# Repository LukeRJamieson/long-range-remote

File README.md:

# Long-range universal remote (Lite, 4 × AA)

A hand-held universal IR remote with far more range than a normal one. A head of 66 narrow-beam
(±5°) SFH 4545 emitters sits at the front of a 107 × 52 × 170 mm block. Behind it are:

- the Waveshare **ESP32-S3-RLCD-4.2** display, at the front of the top deck;
- a D-pad, a SELECT key and a BACK key behind the display, under your thumbs, so your hands never
  cover the screen;
- a bay for **four AA NiMH cells** underneath, which power the LEDs only. You take them out and
  charge them in any NiMH charger. The display board and ESP32 run from the display board's own
  18650, charged through its USB-C.

Everything is menu driven from the screen, or from a phone over Wi-Fi.

There are two boards, both within JLCPCB's cheapest 100 × 100 mm tier:

| Board | Size | What's on it |
|---|---|---|
| LED head | 99.8 × 44.8 mm, R3 corners | 66 × SFH 4545 (14 × 5 grid, corners left for the M3 holes) in 33 strings of 2, one 24 Ω 1206 resistor per string |
| Control | 82 × 52 mm | D-pad + SELECT + BACK (six 6 mm keys, straight to ESP32 GPIOs), the ESP32-switched power gate for the AA pack, the LED switch (a logic-level MOSFET driven straight from a GPIO), the pack-voltage divider, display and LED-head connectors |

KiCad 7 format; it opens in KiCad 7, 8 or 9.

## The system

```
 FRONT                                   top deck (lid)                                     BACK
 ┌──────────────┐  10-way ribbon  ┌────────────────────────┐ 16-way ribbon ┌──────────────────────┐
 │  LED HEAD    │◄════════════════│ CONTROL BOARD  82 x 52 │══════════════►│ Waveshare            │
 │ 99.8 x 44.8  │ J1 ↔ J5         │ D-pad, SELECT, BACK    │ J2 ↔ header   │ ESP32-S3-RLCD-4.2    │
 │ 66×SFH 4545  │ odd = LED_PWR   │ power gate (back)      │               │ (own 18650, USB-C)   │
 │ 33 × 24 Ω    │ even = LED_RTN  │ LED switch (back)      │               └──────────────────────┘
 └──────────────┘                 └────────────────────────┘
                                    ▲ J1 (XH): 4 × AA NiMH holder, under the display
```

## Design notes

| | |
|---|---|
| Strings | 33 × (2 LEDs + 24 Ω) straight off the AA pack |
| LED current per string | 100 mA on fresh cells (5.4 V), 75–83 mA for most of the discharge (4.8–5.0 V), ~58 mA nearly flat (4.4 V) |
| LED current, total | ≤ 3.3 A peak, ~0.87 A average while sending (C1/C2 supply the peaks) |
| Power | 4 × AA NiMH in a Keystone 2478 holder → J1 → P-FET power gate driven by the ESP32 (no switch). Display: its own 18650 |
| LED switching | One low-side AOD424 (DPAK, fully on at 2.5 V) driven straight from GPIO17 through R6 47 Ω; the power gate (ARM) powers the LEDs |
| Battery level | Pack ÷ 2 on GPIO1, and the screen's 18650 on GPIO4 |
| Parts cost | $75.08 AUD ex GST + US$6.21 at Digi-Key/Mouser, $7.15 at Core Electronics (plus the display board and AA cells) |

- **Why 24 Ω:** NiMH cells straight off the charger sit at about 1.35 V each under this load. 24 Ω
  holds the strings to the SFH 4545's 100 mA rating then; for the long flat middle of the
  discharge (1.2–1.25 V a cell) they get 75–83 mA.
- **Runtime:** with ~2000 mAh cells, about 2.3 hours of *continuous* transmitting, which is tens of
  thousands of key presses. Idle, the pack feeds only the 5 µA pack-sense divider (the LEDs are
  disconnected), far less than the cells' own self-discharge. How long the screen
  side lasts depends on the display board's 18650 (the remote never sleeps, so charge it or leave it on USB).
- **No power switch.** The ESP32 connects the pack to the LEDs only while it sends: ARM (GPIO2) →
  R16 10k → Q6 2N3904 pulls Q5's gate to GND through R15 10k. Q5 is an IPD80P03P4L-07 P-MOSFET (DPAK,
  12 mΩ) between J1 and VBAT; R14 100k holds it off whenever ARM is low or the ESP32 is in reset,
  so the pack and the LEDs are disconnected and nothing can light.
  - C7 100 nF from gate to drain is a soft start: the drain rises ~2 V/ms, so C1/C2 charge at ~2 A.
  - C8 1 µF from gate to source keeps Q5 off when cells go in. Without it, C7 would pull the gate low
    as the pack connects and jump-charge C1/C2 at 10–20 A.
  - Together they make Q5 slow to turn on, so the firmware waits 30 ms after raising ARM.
  - The pack is read at J1 (R12/R13 470k), before Q5, so the header shows `AA nn%` any time and
    `AA out` with no cells in.
  - To turn the screen off, use the display board's own PWR button (long press).
- **LED power in firmware.** Menu → *LED power* or the web page's Settings tab: Full / Half / Low =
  100 / 50 / 25 % of the carrier's on-time (`LED_POWER_PCT`). LED current falls in proportion, the
  signal the receiver sees by −4.6 / −10.8 dB (range ~×0.6 / ×0.3 on the same receiver noise floor,
  roughly; check it on your TV). Handy for close range and for saving the cells.
- **Use NiMH, not alkalines.** Four fresh alkalines read 6.0–6.4 V, which would push the strings
  well past 100 mA. Low-self-discharge cells (eneloop-type) keep their charge in a drawer.
- **When to swap cells:** the header shows `AA nn%` (or `AA out`) and the screen's own battery
  (`scr nn%`). Below 4.6 V it says "AA cells low". Below **4.4 V at rest it stops sending** ("AA cells
  flat"): that is 1.1 V a cell, flat for NiMH. Q2's gate drive comes from the ESP32's 3.3 V, so the LED
  switch works the same right down to that point.
- **Carrier duty is capped at 50 %** (`LED_DUTY_MAX_PCT`), whatever a code or `.ir` file asks for: on
  fresh cells the strings peak at ~110 mA, so the average must stay well under the SFH 4545's 100 mA
  DC rating.
- **Check J1's polarity when you crimp the holder's plug** (red = pin 1, BATT). There is no
  reverse-polarity protection: a reversed pack would drive Q5's body diode and the electrolytics
  backwards.
- **Safety interlock:** the LEDs only light while ARM *and* IR_DRV are high. ARM (through Q6 and Q5)
  powers the LEDs, and IR_DRV switches Q2. The firmware starts the carrier `LED_ARM_SETTLE_MS` (30 ms)
  after ARM, once VBAT is up, and checks the pack before every frame. A held key stops after 15 s. It is still a strong IR source, so don't look into the
  head up close.
- **The ±5° beam needs a little aiming,** but less than you'd think. At 3 m the spot is about 50 cm
  across, and indoors, walls and ceiling reflect enough to reach a TV's sensor off-axis.
- **No sleep:** the firmware stays fully on (screen, keys, Wi-Fi and web page) until you switch it
  off with the display board's PWR button.

## Files

| Path | What it is |
|---|---|
| `docs/Long-Range_Remote_Lite_User_Guide.pdf` | **User guide**: setup, using the remote, batteries, the web page, home Wi-Fi, building the housing, troubleshooting |
| `led_head_lite/led_head_lite.kicad_pro` | LED head project (schematic + PCB) |
| `control_lite/control_lite.kicad_pro` | Control board project (schematic + routed PCB) |
| `gerbers/*_jlcpcb.zip` | Gerber + drill zips, ready to upload to JLCPCB |
| `bom/lite_digikey_bom.csv` | BOM with refs, prices and stock |
| `bom/lite_digikey_upload.csv` | Digi-Key BOM-manager upload |
| `bom/lite_core_electronics.csv` | Display ribbon and header (Core Electronics) |
| `firmware/LongRangeRemote/` | **Universal remote firmware**: TVs, AV receivers, set-top boxes, soundbars, projectors, hi-fi, air-cons..., phone web remote. See its README |
| `firmware/sd_card/irdb.bin` | **The IR code database (~6,800 remotes). Copy it to the SD card**: all codes live on the card, not in the firmware |
| `firmware/sd_card/wifi.example.txt` | Example of `wifi.txt`, the home Wi-Fi file on the card. The remote creates and updates `wifi.txt` itself (Menu → Wi-Fi network); this is for setting it on a PC |
| `firmware/bringup/bringup.ino` | Bring-up firmware: keys, NEC transmit, LED arming, battery voltage |
| `previews/*_front.png`, `*_back.png`, `*_schematic.png` | Both sides of each board and the schematics |
| `previews/*_3d_*.png` | 3D renders of both boards with their components (front, back, three-quarter views) |
| `pdf/` | Printable PDFs: `*_schematic.pdf`, and `*_pcb.pdf` with top/bottom copper, top/bottom assembly and a 1:1 page to print at 100 % for checking fit |
| `housing/` | 3D-printable housing (Prusa MINI): STEP for Fusion 360, print-ready STLs, parametric CadQuery source. See `housing/README.md` |
| `tools/` | Generators (see "Regenerating"). `tools/bin/` is where Freerouting goes if you re-autoroute (not included: 64 MB) |
| `sim/control_lite_sim.py` | ngspice simulations of the control board + LED head: cell insertion, power-gate turn-on/off, 38 kHz drive, switching transients over the ribbon, worst cases (needs ngspice) |

The `_lite` in the board and file names is historical: this is the only version.

## Boards

### LED head (99.8 × 44.8 mm, R3 corners)

- **Front:** 66 × SFH 4545 on a 14 × 5 grid (6.8 mm along a row, 7.0 mm between rows), rows of
  12 / 14 / 14 / 14 / 12. The four corner positions are left empty for the M3 holes at (±44.2, ±14.0).
- **Back:** 33 × 24 Ω resistors, plus J1.
  - The resistors are 1206 SMD with hand-solder pads (Panasonic ERJ-P08J240V, 0.66 W,
    pulse-withstanding), in the bands between the LED rows, each right behind its string's last LED.
  - Each sees up to 0.24 W, but only while a carrier pulse is on.
  - Solder them before the LEDs, while the back is still flat.
- **J1** is a plain 2 × 5 pin header on the back, along the bottom edge, centred. Odd pins are
  LED_PWR and even pins LED_RTN, so a reversed plug only puts about 3 V of reverse bias on each LED
  (under the 5 V rating) and nothing lights. Mark pin 1 on the socket anyway.
- **Copper:** the F.Cu pour is LED_PWR (it feeds every string's first anode); the B.Cu pour is
  LED_RTN. No trace turns at a right angle.

### Control board (82 × 52 mm)

**Front (facing up through the lid): the six keys and nothing else.**
- SW1–SW4: 6 mm D-pad (Omron B3F-1000) on the left; SW5 SELECT, the same switch, on the right (the
  housing gives it a round cap); SW6 BACK at the D-pad's lower right (a square cap).

**Back (everything else, hanging into the tray):** the ribbon connectors, the LED switch (Q2, a DPAK
soldered on the back, right under J5), the reservoir capacitors, the AA plug, and the power gate (Q5,
also a DPAK, with Q6, R14, R15, R16, C7 and C8) behind SELECT's right-hand side.

```
 J1 BATT (4 x AA) ──┬── R12/R13 470k ÷ 2 ── GPIO1 (pack voltage, always readable)
                    └── Q5 IPD80P03P4L-07 (P-FET) ── VBAT ──┬── C1, C2 470 µF, C3 100 nF
        gate: R14 100k to BATT, C8 1 µF to BATT,             ├── J5 odd pins ──► LED strings
              C7 100 nF to VBAT (soft start);
              Q6 2N3904 pulls it to GND via R15 when ARM (GPIO2) is high
                                                   LED_RTN ◄── J5 even pins
 IR_DRV (GPIO17, 38 kHz) ── R6 47 Ω ── Q2 AOD424 (low side, logic level) ── GND
```

- **Pull-downs:** R4 (100 k) keeps Q6 off while the ESP32 boots, and R7 (100 k) holds IR_DRV, and
  through R6 Q2's gate, low.
- **Q2 needs no gate driver:** the AOD424 is specified at 2.5 V gate drive (5.7 mΩ max), so the 3.3 V
  GPIO turns it fully on. R6 47 Ω plus the GPIO's own resistance (drive strength 2) slows its switching
  edge on purpose: a fast edge makes the ribbon ring and reverse-biases the LEDs past their 5 V rating.
  With 47 Ω there is none, the GPIO peaks at ~36 mA, and Q2 dissipates under 0.1 W (`sim/`).
- **Keys:** each key shorts its own ESP32 GPIO to GND (see the J2 table). The ESP32's internal
  pull-ups (about 45 kΩ) hold the pins high, so there are no key resistors and no expander.
  - R11 (1 kΩ) sits in series with RIGHT, on GPIO43. That pin is UART0 TX, which the ESP32's boot
    ROM drives for a moment at power-up; the resistor limits a key held then to 3.3 mA.
  - BACK is on GPIO14, the display board's I2C clock (SCL), the only free header pin that isn't USB.
    The display board's own pull-up holds it high. The firmware only uses that I2C bus for ~30 ms at
    start-up (to set up the speaker's codec), and SCL pulled low while SDA stays high is never an I2C
    start, so the display board's chips ignore the key.
  - The firmware debounces in software.
- Power tracks (BATT, VBAT, LED_RTN) are 1.5 mm, with GND poured on both layers. No track turns at a
  right angle: corners the autorouter leaves are cut to 45° when the board is generated.

## Connections

### Ribbons (straight-through: pin n = pin n)

| Cable | Ends | Pinout |
|---|---|---|
| 10-way (Adafruit 370, 6") | LED head J1 ↔ control J5 | odd pins LED_PWR, even pins LED_RTN (5 conductors each way) |
| 16-way (Adafruit 2 × 8, 12", **cut to ~70 mm**) | control J2 ↔ Waveshare header | see below |

`tools/check_system.py` checks both ribbons pin by pin, and that the firmware's pin numbers
(`config.h`) match the GPIO each J2 net lands on.

**Shorten the 16-way ribbon before fitting it.** Both of its ends are in the lid (the display header
and J2 are about 50 mm apart along the ribbon's route), and there is no room for 30 cm of ribbon.
Cut it so ~70 mm remains between socket centres, and press one of the CNC Tech 3030-16-0102-00
sockets (Digi-Key LKC16H-ND, in the BOM) onto the cut end in a vice, with a scrap of wood each side.
Copy the original socket at the other end: the red stripe at the same end and the polarising key
on the same face of the ribbon, so it stays straight-through (pin n = pin n). Check with a
multimeter that pin 1 goes to pin 1 and pin 16 to pin 16 before plugging it in.

**Routing (housing):** the two ribbons share the ~3 mm gap between the battery bay's roof and the
display's 18650 cell (it hangs below the display board in an open cradle). Lay them side by side, flat:
the 10-way on the left half of the roof (towards J5), the 16-way on the right half (towards J2).

### Control J2 ↔ Waveshare 2 × 8 header

| J2 pin | Waveshare | Used for | | J2 pin | Waveshare | Used for |
|---|---|---|---|---|---|---|
| 1 | 3V3 | — (not used) | | 2 | VBUS | — (not used) |
| 3 | GND | GND | | 4 | GND | GND |
| 5 | **GPIO0** | **SELECT** key (also BOOT) | | 6 | GPIO19 | — (USB) |
| 7 | **GPIO1** | **AA pack ÷ 2** (ADC) | | 8 | GPIO20 | — (USB) |
| 9 | **GPIO2** | **ARM** | | 10 | **U0TXD (GPIO43)** | **RIGHT** key, through R11 1 k |
| 11 | **GPIO3** | **DOWN** key | | 12 | **U0RXD (GPIO44)** | **LEFT** key |
| 13 | **GPIO17** | **IR_DRV** (RMT, 38 kHz carrier) | | 14 | SDA (GPIO13) | — (not used) |
| 15 | **GPIO18** | **UP** key | | 16 | **SCL (GPIO14)** | **BACK** key (display board's I2C pull-up) |

The keys use pins the Waveshare board brings out but doesn't need:
- **GPIO0** is the BOOT strap: holding SELECT through a reset starts the bootloader.
- **GPIO43 / GPIO44 (UART0):** the board's USB-C goes to the ESP32-S3's own USB, so the serial
  monitor and flashing don't use UART0.
- **GPIO18** is also the Waveshare board's own KEY button (active low). It is in parallel with
  UP, so that button works as UP too.
- UP is on pin 15 and SELECT on pin 5 because pin 15 is at the D-pad's end of the header and pin 5
  at SELECT's: neither key's track has to cross the others on the control board.
- GPIO3 is a strapping pin, but its strap function is unused by default.
- **GPIO14** is the display board's I2C SCL. The firmware only uses that bus once, for ~30 ms at
  start-up, to set up the speaker's ES8311 codec, then gives the pin back to BACK (see Keys above).
  If you add I2C code later, do the same: borrow the pin, never while BACK is held, and hand it back.

**Waveshare end of the 16-way ribbon:**
- The Waveshare header is female, so push two 8-pin pieces of Pololu double-sided header into the
  ribbon socket to make it a plug.
- Put the red stripe (pin 1) on 3V3. Looking at the display board from the back with its 18650 at the
  bottom, **pin 1 (3V3) is the bottom-left pin** (checked on a real board). The bottom row, nearest the
  18650 holder, is the odd pins, reading 3V3, GND, GP0 … GP18 left to right; the top row is the even
  pins, VBUS, GND, GP19 … SCL. The socket isn't keyed, and a ribbon plugged in the wrong way
  round puts 3.3 V on the BACK key's line (pressing BACK would then short the display's 3.3 V supply).
  To check, plug the ribbon into the display only, power the display from USB, and measure 3.3 V between
  pins 1 and 3 of the ribbon's free socket (the control board end) before plugging that end in.

## Firmware

**`firmware/LongRangeRemote/` is the firmware to use.** It is a universal remote:
- **all IR codes on the SD card** (`firmware/sd_card/irdb.bin`): about 1,890 brands, 10,670
  remotes and 530,000 codes from Flipper-IRDB, IRDB, LIRC, JP1 and SmartIR. Update them by swapping the file or
  uploading it from your phone, without reflashing;
- set-top-box protocols such as DirecTV, Dish, Motorola and TiVo, pre-rendered with
  IrpTransmogrifier;
- TV functions including channel-number entry, colour keys, guide and HDMI inputs;
- a BACK key that goes one screen back from anywhere;
- Vol / Nav pads that turn the keys into the device's own keys;
- code search ordered by how common each code is;
- your own Flipper `.ir` files from the SD card;
- a phone web remote;
- LED power levels (Full / Half / Low);
- key sounds on the display board's speaker, with volume and mute (Menu → Sound).

Build it with Partition Scheme "16M Flash (3MB APP/9.9MB FATFS)" and **OPI PSRAM**, which holds
the index of the code database (the codes themselves are read from the SD card). Then put `irdb.bin` on a FAT32 microSD card. See `firmware/LongRangeRemote/README.md`.

### Bring-up firmware

`firmware/bringup/bringup.ino` is a minimal test of the hardware. It is for Arduino-ESP32 core 3.x
and compiles cleanly for the ESP32-S3 with all warnings on.

| Key | Action |
|---|---|
| Up / Down | Step through the code list |
| Left / Right | Step through the device list |
| SELECT | Sends the selected NEC code (holding it sends NEC repeat frames) and prints the pack voltage, with a warning below 4.6 V |
| BACK | Back to the first code of the first device (and shows GPIO14 reads) |

The Serial prints in `printSelection()` and `handleButtons()` mark where your on-screen menu hooks in.

Each transmission follows this sequence:

1. Check the pack (nothing is sent with no cells in).
2. Raise ARM.
3. Wait 30 ms for the power gate.
4. Send with the RMT peripheral (38 kHz carrier, 33 % duty, idle low).
5. Drop ARM.

The code table is placeholder NEC codes. Capture your own devices' codes and replace it.

Never hold IR_DRV high, and don't look into the head at close range.

## Bill of materials

Prices were checked **3–4 Oct 2026**; on 12 Oct the main lines (LEDs, 24R resistors, AOD424, IPD80P03P4L-07,
470 µF, 100 nF, 1 µF, 2N3904, 10-way header, the new IDC socket) were rechecked as in stock at Digi-Key AU. Digi-Key Australia prices are **AUD ex GST**; Core Electronics
prices are **AUD inc GST**.

| | Cost |
|---|---|
| **Digi-Key**, everything except the parts below | **$75.08 AUD ex GST** |
| 33 × ERJ-P08J240V, IPD80P03P4L-07, 2N3904, Keystone 2478 holder | **US$6.21**, priced from Digi-Key US or Mouser US; the upload file lists them by manufacturer part number |
| JST XHP-2 plug + SXH-001T-P0.6 crimps for the AA holder's leads | in the upload file by part number; prices not checked (you also need an XH crimp tool) |
| **Core Electronics** (16-way ribbon, header) | **$7.15 AUD inc GST** |

**Not included:** the Waveshare ESP32-S3-RLCD-4.2, four AA NiMH cells and a charger, an
**unprotected** 18650 for the display board (it has its own protection: S8261 + 8205; protected cells are a
few mm longer and may not fit its holder), the PCBs, and the housing hardware (see `housing/README.md`). The LED head's 2 × 5 header is
two 5-pin pieces of the Core Electronics header strip.

## Ordering the PCBs (JLCPCB)

Upload each `gerbers/*_jlcpcb.zip` with:

- **Board:** 2 layers, 1.6 mm, 1 oz copper, HASL.
- **Board sizes:** 99.8 × 44.8 mm (LED head) and 82 × 52 mm (control).
- Each zip has the 7 layers (copper, mask and silkscreen both sides, outline) and separate plated
  (`-PTH.drl`) and non-plated (`-NPTH.drl`, the four M3 holes) drill files. Smallest features:
  0.4 mm via drill, 0.35 mm annular ring, 0.2 mm clearance, silkscreen 1.0 mm text / 0.15 mm lines,
  all inside JLCPCB's standard 2-layer process.
- JLCPCB prints its order number on the silkscreen unless you choose "Remove Mark" (small fee) or
  "Specify a location"; neither board has a marked spot, so remove it or accept where they put it.

## Before ordering / building

1. **Run DRC in your own KiCad.** Expected: 0 errors, 0 unconnected, 0 warnings on both boards.
   DRC only checks rules, so `tools/build_all.sh` also runs `tools/check_layout.py`, which fails the
   build on legal-but-poor layout: pads within 1.5 mm of the board edge, a two-pin part more than
   12 mm from the rest of its net, and tracks more than 1.5 x (and 8 mm) longer than their pads'
   spread. The few deliberate exceptions are listed in the script, each with its reason.
2. **Check the LEDs before soldering 66 of them.** Confirm the SFH 4545's 2.54 mm lead pitch and
   that cathode = pin 1 (the flat side on the silkscreen) against a real part.
3. **Check the 2N3904 (Q6) pin order** against your part: the footprint is E-B-C (pads 1-2-3), as on onsemi's 2N3904BU.
   Fit it with its flat side matching the silkscreen.
4. **R6 is 47 Ω and GPIO17 stays at drive strength 2.** Together they slow Q2's switching edge on
   purpose: a much faster edge makes the ribbon ring and reverse-bias the LEDs past their 5 V rating at
   every carrier cycle (see `sim/`).
   Q2 and Q5 are DPAKs on the back: solder the tab with a hot iron (or hot air) before the leads.
5. **Crimp the AA holder's plug with red (+) on pin 1** (BATT). The board has no reverse-polarity protection:
   a reversed plug puts −5 V on the 470 µF capacitors.
6. **First power-up:**
   - Leave the LED head unplugged and put the cells in.
   - Check that VBAT (J5 pin 1) is 0 V, and only rises to the pack voltage, within about 30 ms, while
     ARM is high (press a key).
   - Then plug the head in and send a code.

## Regenerating

You need:

- **KiCad 7+:** the `pcbnew` Python module plus `kicad-cli`.
- **Python 3:** `cairosvg` and `Pillow` (for the previews), `reportlab` and `pypdf` (for the PDFs).
- **Freerouting, only to re-autoroute:** Java 17+ and [Freerouting](https://github.com/freerouting/freerouting/releases)
  2.1.0 saved as `tools/bin/freerouting.jar`.
- **3D renders only:** `cadquery` (OpenCascade) and `vtk`, plus KiCad's 3D models for the parts used.
  `tools/render_3d.py --fetch MODELS_DIR` downloads just those from KiCad's packages3D repository.

```sh
tools/build_all.sh            # rebuild everything, re-using the saved control-board route (*.ses)
tools/build_all.sh --reroute  # also re-run the autorouter (after moving parts)
tools/render_3d.py MODELS_DIR # 3D renders of both boards into previews/
```

The generators rebuild each board from scratch. Once you start editing in KiCad, treat the KiCad
files as the source of truth.

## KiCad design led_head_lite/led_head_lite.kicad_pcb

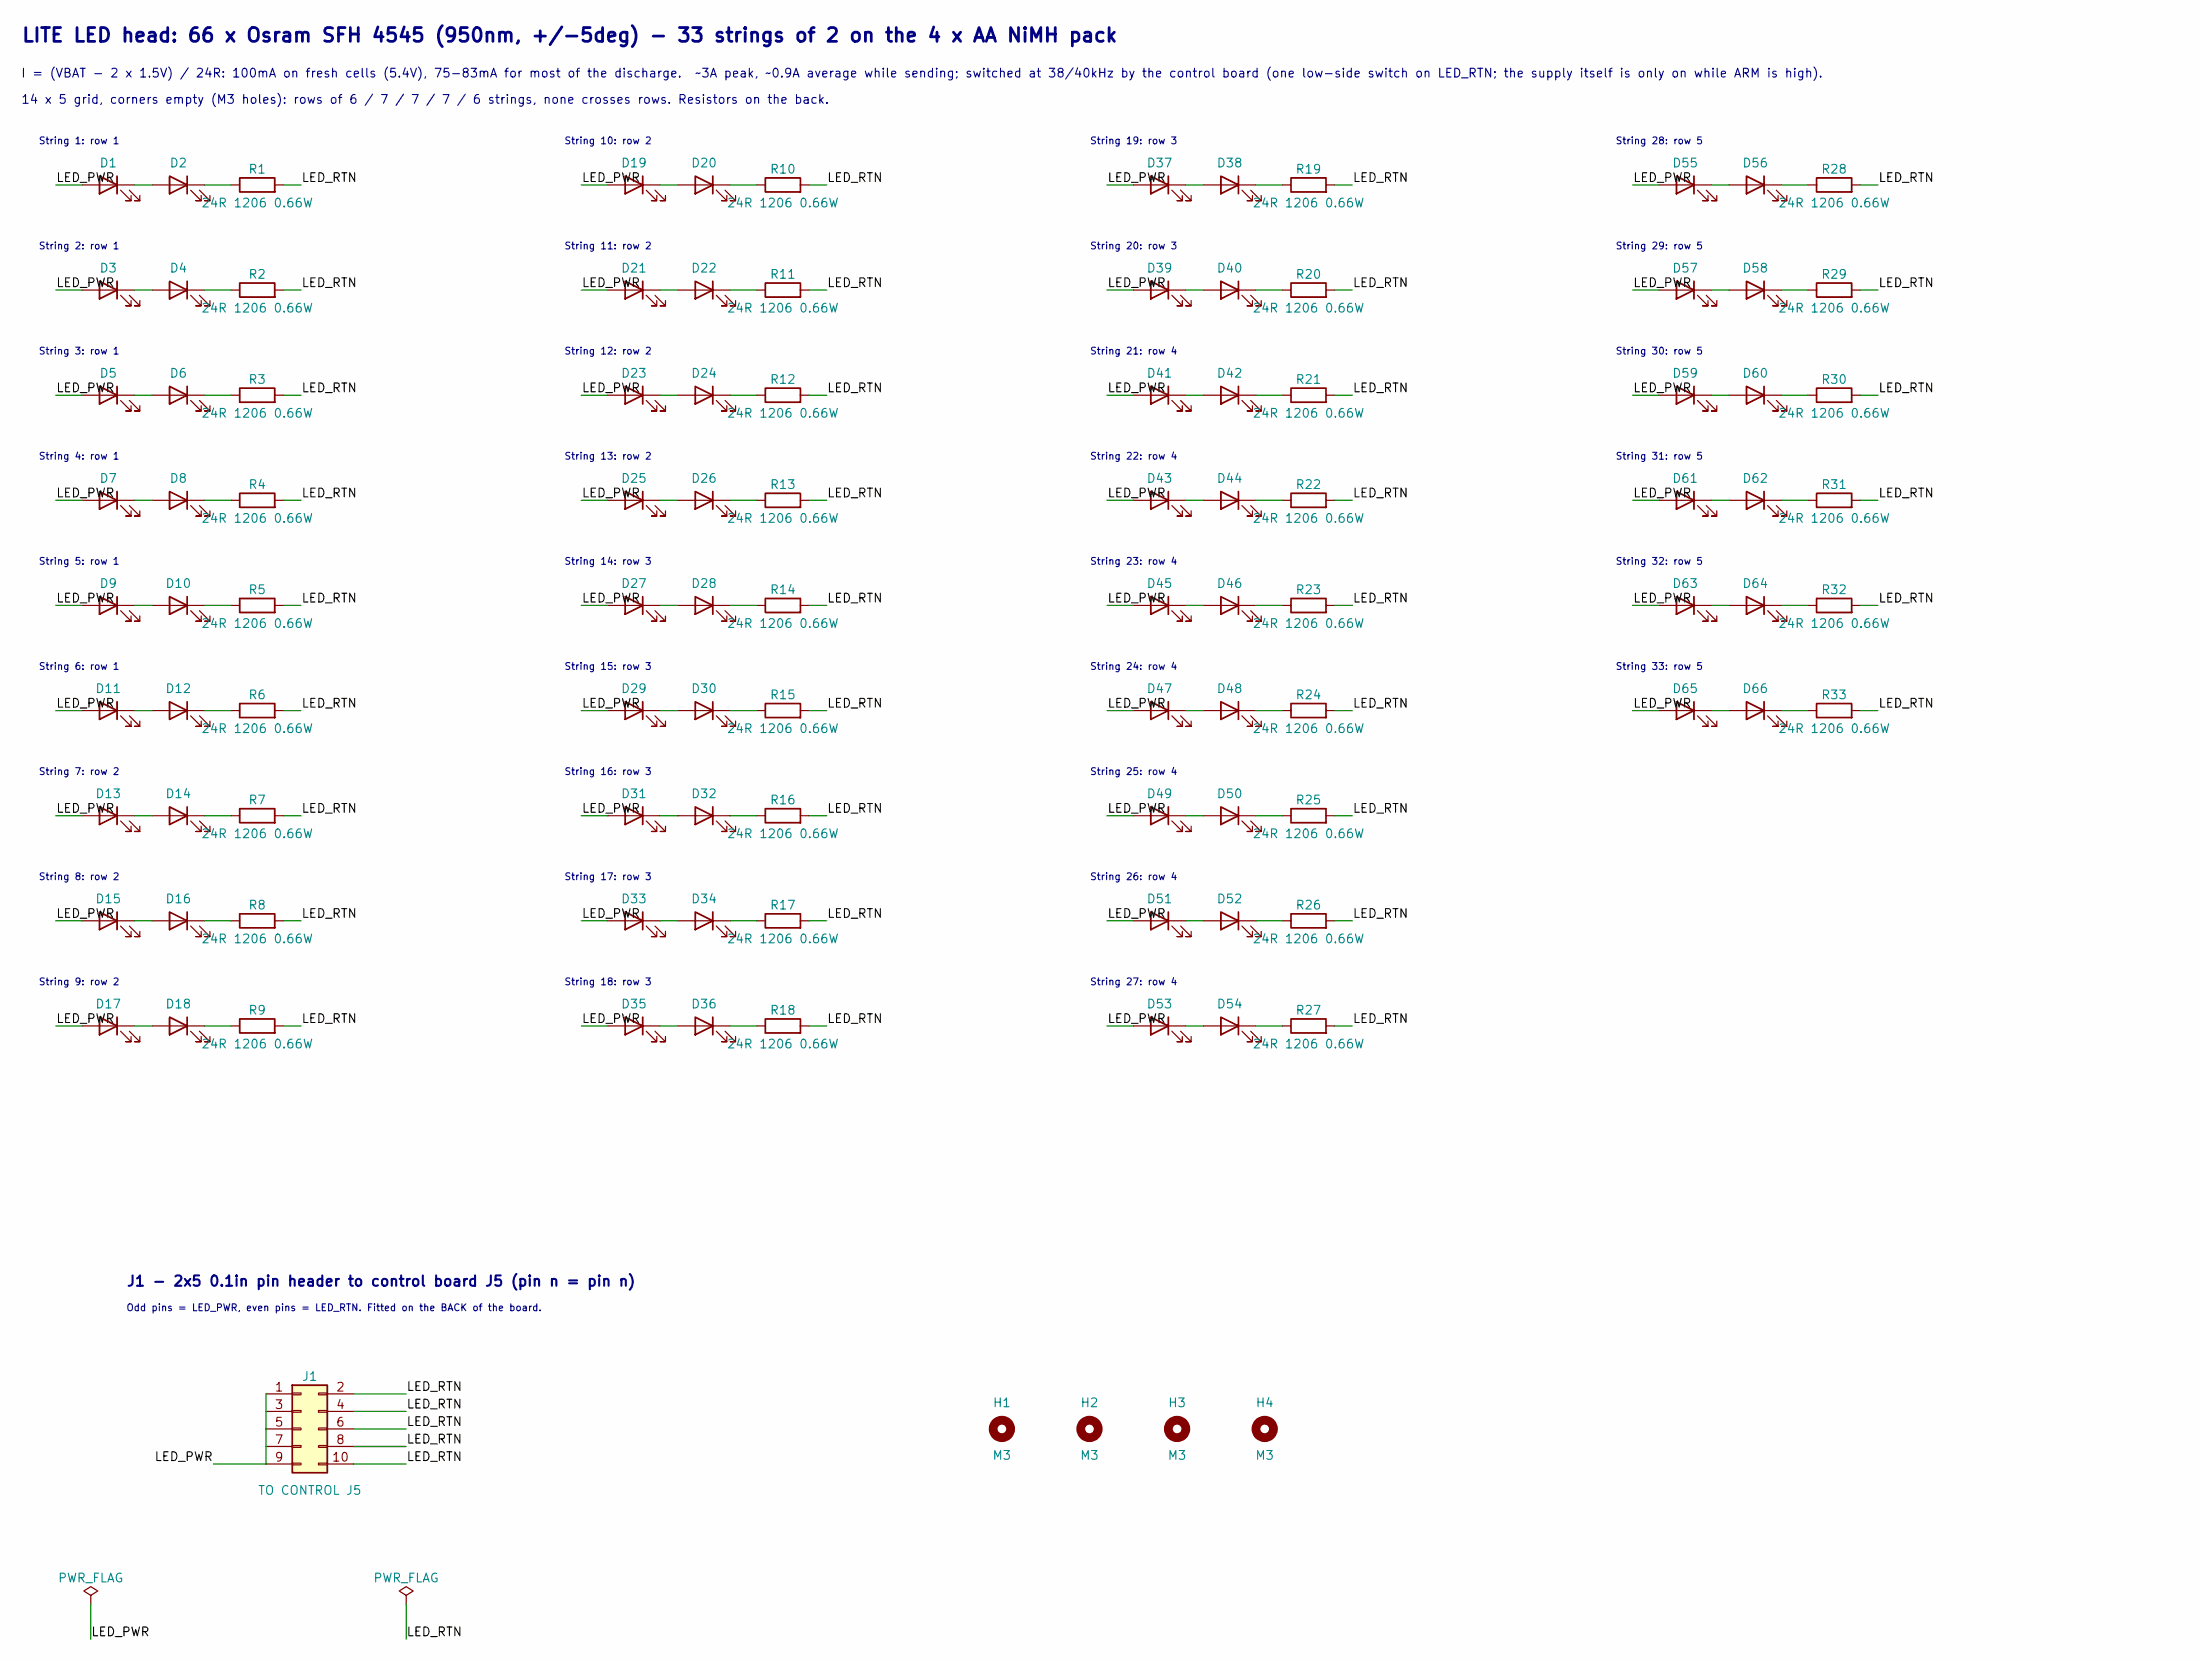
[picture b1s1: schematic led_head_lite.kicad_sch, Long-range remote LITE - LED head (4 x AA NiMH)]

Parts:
D1, D2, D3, D4, D5, D6, D7, D8, D9, D10, D11, D12, D13, D14, D15, D16, D17, D18, D19, D20, D21, D22, D23, D24, D25, D26, D27, D28, D29, D30, D31, D32, D33, D34, D35, D36, D37, D38, D39, D40, D41, D42, D43, D44, D45, D46, D47, D48, D49, D50, D51, D52, D53, D54, D55, D56, D57, D58, D59, D60, D61, D62, D63, D64, D65, D66: SFH 4545; LED_D5.0mm
H1, H2, H3, H4: M3; MountingHole_3.2mm_M3
J1: TO CONTROL J5; PinHeader_2x05_P2.54mm_Vertical; MPN Sullins PRPC005DAAN-RC
R1, R2, R3, R4, R5, R6, R7, R8, R9, R10, R11, R12, R13, R14, R15, R16, R17, R18, R19, R20, R21, R22, R23, R24, R25, R26, R27, R28, R29, R30, R31, R32, R33: 24R 1206 0.66W; R_1206_3216Metric_Pad1.30x1.75mm_HandSolder; MPN Panasonic ERJ-P08J240V

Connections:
/LED_PWR: D1.2 (A), D3.2 (A), D5.2 (A), D7.2 (A), D9.2 (A), D11.2 (A), D13.2 (A), D15.2 (A), D17.2 (A), D19.2 (A), D21.2 (A), D23.2 (A), D25.2 (A), D27.2 (A), D29.2 (A), D31.2 (A), D33.2 (A), D35.2 (A), D37.2 (A), D39.2 (A), D41.2 (A), D43.2 (A), D45.2 (A), D47.2 (A), D49.2 (A), D51.2 (A), D53.2 (A), D55.2 (A), D57.2 (A), D59.2 (A), D61.2 (A), D63.2 (A), D65.2 (A), J1.1, J1.3, J1.5, J1.7, J1.9
/LED_RTN: J1.2, J1.4, J1.6, J1.8, J1.10, R1.2, R2.2, R3.2, R4.2, R5.2, R6.2, R7.2, R8.2, R9.2, R10.2, R11.2, R12.2, R13.2, R14.2, R15.2, R16.2, R17.2, R18.2, R19.2, R20.2, R21.2, R22.2, R23.2, R24.2, R25.2, R26.2, R27.2, R28.2, R29.2, R30.2, R31.2, R32.2, R33.2
unnamed: D1.1 (K), D2.2 (A)
unnamed: D2.1 (K), R1.1
unnamed: D3.1 (K), D4.2 (A)
unnamed: D4.1 (K), R2.1
unnamed: D5.1 (K), D6.2 (A)
unnamed: D6.1 (K), R3.1
unnamed: D7.1 (K), D8.2 (A)
unnamed: D8.1 (K), R4.1
unnamed: D9.1 (K), D10.2 (A)
unnamed: D10.1 (K), R5.1
unnamed: D11.1 (K), D12.2 (A)
unnamed: D12.1 (K), R6.1
unnamed: D13.1 (K), D14.2 (A)
unnamed: D14.1 (K), R7.1
unnamed: D15.1 (K), D16.2 (A)
unnamed: D16.1 (K), R8.1
unnamed: D17.1 (K), D18.2 (A)
unnamed: D18.1 (K), R9.1
unnamed: D19.1 (K), D20.2 (A)
unnamed: D20.1 (K), R10.1
unnamed: D21.1 (K), D22.2 (A)
unnamed: D22.1 (K), R11.1
unnamed: D23.1 (K), D24.2 (A)
unnamed: D24.1 (K), R12.1
unnamed: D25.1 (K), D26.2 (A)
unnamed: D26.1 (K), R13.1
unnamed: D27.1 (K), D28.2 (A)
unnamed: D28.1 (K), R14.1
unnamed: D29.1 (K), D30.2 (A)
unnamed: D30.1 (K), R15.1
unnamed: D31.1 (K), D32.2 (A)
unnamed: D32.1 (K), R16.1
unnamed: D33.1 (K), D34.2 (A)
unnamed: D34.1 (K), R17.1
unnamed: D35.1 (K), D36.2 (A)
unnamed: D36.1 (K), R18.1
unnamed: D37.1 (K), D38.2 (A)
unnamed: D38.1 (K), R19.1
unnamed: D39.1 (K), D40.2 (A)
unnamed: D40.1 (K), R20.1
unnamed: D41.1 (K), D42.2 (A)
unnamed: D42.1 (K), R21.1
unnamed: D43.1 (K), D44.2 (A)
unnamed: D44.1 (K), R22.1
unnamed: D45.1 (K), D46.2 (A)
unnamed: D46.1 (K), R23.1
unnamed: D47.1 (K), D48.2 (A)
unnamed: D48.1 (K), R24.1
unnamed: D49.1 (K), D50.2 (A)
unnamed: D50.1 (K), R25.1
unnamed: D51.1 (K), D52.2 (A)
unnamed: D52.1 (K), R26.1
unnamed: D53.1 (K), D54.2 (A)
unnamed: D54.1 (K), R27.1
unnamed: D55.1 (K), D56.2 (A)
unnamed: D56.1 (K), R28.1
unnamed: D57.1 (K), D58.2 (A)
unnamed: D58.1 (K), R29.1
unnamed: D59.1 (K), D60.2 (A)
unnamed: D60.1 (K), R30.1
unnamed: D61.1 (K), D62.2 (A)
unnamed: D62.1 (K), R31.1
unnamed: D63.1 (K), D64.2 (A)
unnamed: D64.1 (K), R32.1
unnamed: D65.1 (K), D66.2 (A)
unnamed: D66.1 (K), R33.1

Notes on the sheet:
LITE LED head: 66 x Osram SFH 4545 (950nm, +/-5deg) - 33 strings of 2 on the 4 x AA NiMH pack
I = (VBAT - 2 x 1.5V) / 24R: 100mA on fresh cells (5.4V), 75-83mA for most of the discharge. ~3A peak, ~0.9A average while sending; switched at 38/40kHz by the control board (one low-side switch on LED_RTN; the supply itself is only on while ARM is high).
14 x 5 grid, corners empty (M3 holes): rows of 6 / 7 / 7 / 7 / 6 strings, none crosses rows. Resistors on the back.
String 1: row 1
String 2: row 1
String 3: row 1
String 4: row 1
String 5: row 1
String 6: row 1
String 7: row 2
String 8: row 2
String 9: row 2
String 10: row 2
String 11: row 2
String 12: row 2
String 13: row 2
String 14: row 3
String 15: row 3
String 16: row 3
String 17: row 3
String 18: row 3
String 19: row 3
String 20: row 3
String 21: row 4
String 22: row 4
String 23: row 4
String 24: row 4
String 25: row 4
String 26: row 4
String 27: row 4
String 28: row 5
String 29: row 5
String 30: row 5
String 31: row 5
String 32: row 5
String 33: row 5
J1 - 2x5 0.1in pin header to control board J5 (pin n = pin n)
Odd pins = LED_PWR, even pins = LED_RTN. Fitted on the BACK of the board.

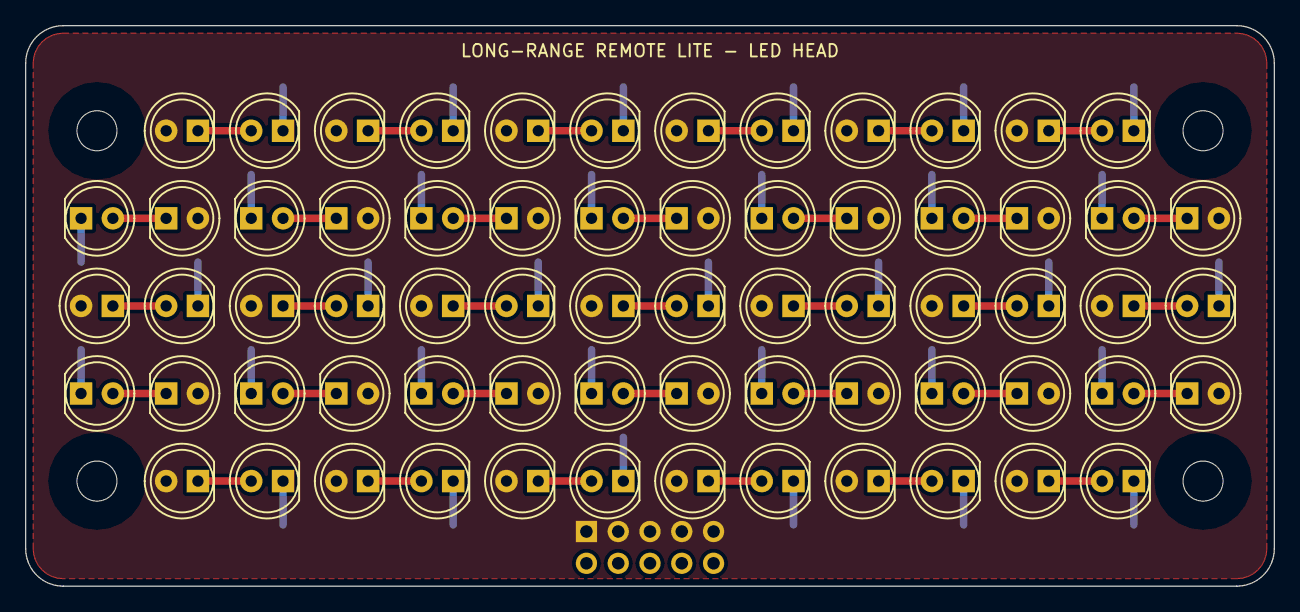
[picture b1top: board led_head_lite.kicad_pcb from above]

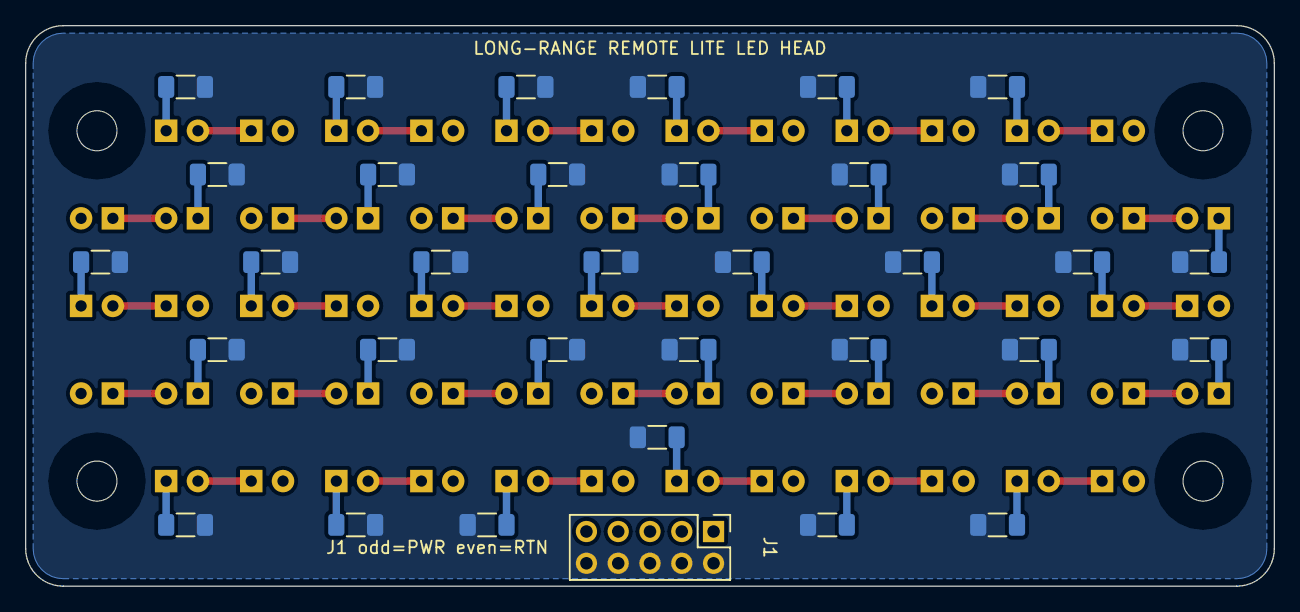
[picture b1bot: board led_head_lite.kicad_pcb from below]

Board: 2 copper layers, 99.8 x 44.8 mm, 104 parts (34 on the bottom side), 68 nets.

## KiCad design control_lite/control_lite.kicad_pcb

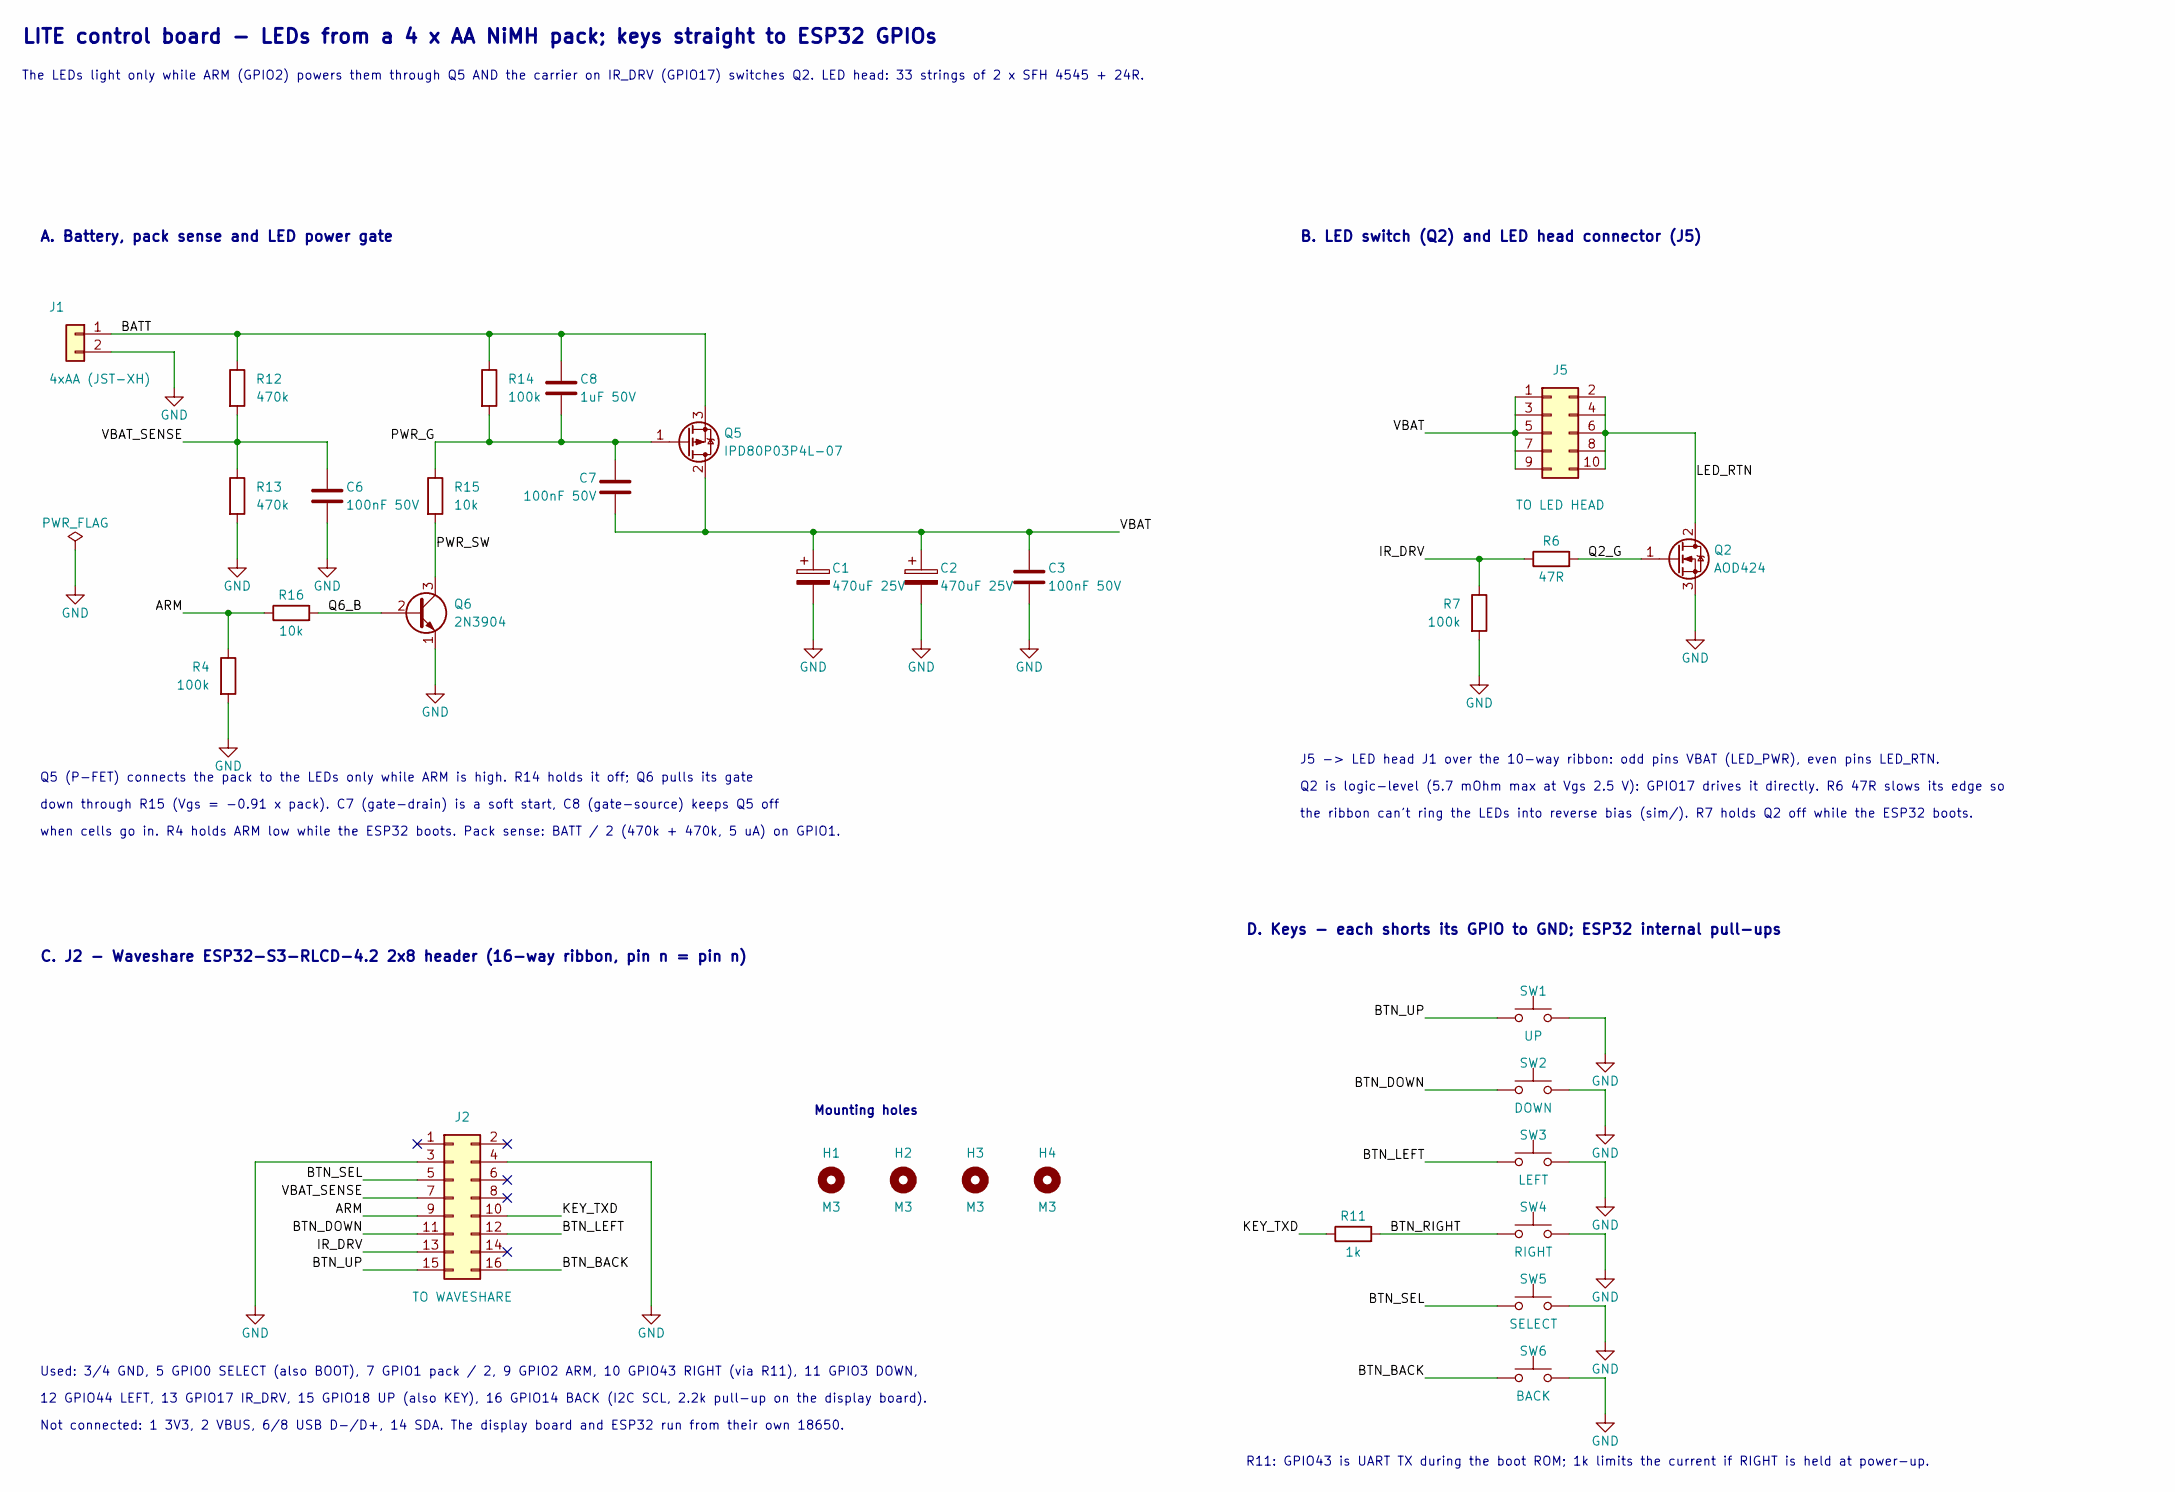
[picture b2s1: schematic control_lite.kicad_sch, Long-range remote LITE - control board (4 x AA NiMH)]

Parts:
C1, C2: 470uF 25V; CP_Radial_D10.0mm_P5.00mm; MPN Panasonic EEU-FR1E471
C3, C6, C7: 100nF 50V; C_Rect_L4.0mm_W2.5mm_P2.50mm; MPN TDK FG18X7R1H104KNT06
C8: 1uF 50V; C_Disc_D5.1mm_W3.2mm_P5.00mm; MPN TDK FG24X7R1H105KRT06
H1, H2, H3, H4: M3; MountingHole_3.2mm_M3
J1: 4xAA (JST-XH); JST_XH_B2B-XH-A_1x02_P2.50mm_Vertical; MPN JST B2B-XH-A
J2: TO WAVESHARE; IDC-Header_2x08_P2.54mm_Vertical; MPN Wurth 61201621621
J5: TO LED HEAD; IDC-Header_2x05_P2.54mm_Vertical; MPN Wurth 61201021621
Q2: AOD424; TO-252-2; MPN Alpha & Omega AOD424
Q5: IPD80P03P4L-07; TO-252-2; MPN Infineon IPD80P03P4L07ATMA2
Q6: 2N3904; TO-92_Inline_Wide; MPN onsemi 2N3904BU
R4, R7, R14: 100k; R_Axial_DIN0207_L6.3mm_D2.5mm_P7.62mm_Horizontal; MPN Yageo MFR-25FBF52-100K
R6: 47R; R_Axial_DIN0207_L6.3mm_D2.5mm_P7.62mm_Horizontal; MPN Yageo MFR-25FBF52-47R
R11: 1k; R_Axial_DIN0207_L6.3mm_D2.5mm_P7.62mm_Horizontal; MPN Yageo MFR-25FBF52-1K
R12, R13: 470k; R_Axial_DIN0207_L6.3mm_D2.5mm_P7.62mm_Horizontal; MPN Yageo MFR-25FBF52-470K
R15, R16: 10k; R_Axial_DIN0207_L6.3mm_D2.5mm_P7.62mm_Horizontal; MPN Yageo MFR-25FBF52-10K
SW1: UP; SW_PUSH_6mm; MPN Omron B3F-1000 (6mm)
SW2: DOWN; SW_PUSH_6mm; MPN Omron B3F-1000 (6mm)
SW3: LEFT; SW_PUSH_6mm; MPN Omron B3F-1000 (6mm)
SW4: RIGHT; SW_PUSH_6mm; MPN Omron B3F-1000 (6mm)
SW5: SELECT; SW_PUSH_6mm; MPN Omron B3F-1000 (6mm)
SW6: BACK; SW_PUSH_6mm; MPN Omron B3F-1000 (6mm)

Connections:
/ARM: J2.9, R4.1, R16.1
/BATT: C8.1, J1.1, Q5.3 (S), R12.1, R14.1
/BTN_BACK: J2.16, SW6.1
/BTN_DOWN: J2.11, SW2.1
/BTN_LEFT: J2.12, SW3.1
/BTN_RIGHT: R11.2, SW4.1
/BTN_SEL: J2.5, SW5.1
/BTN_UP: J2.15, SW1.1
/IR_DRV: J2.13, R6.1, R7.1
/KEY_TXD: J2.10, R11.1
/LED_RTN: J5.2, J5.4, J5.6, J5.8, J5.10, Q2.2 (D)
/PWR_G: C7.1, C8.2, Q5.1 (G), R14.2, R15.1
/PWR_SW: Q6.3 (C), R15.2
/Q2_G: Q2.1 (G), R6.2
/Q6_B: Q6.2 (B), R16.2
/VBAT: C1.1, C2.1, C3.1, C7.2, J5.1, J5.3, J5.5, J5.7, J5.9, Q5.2 (D)
/VBAT_SENSE: C6.1, J2.7, R12.2, R13.1
GND: C1.2, C2.2, C3.2, C6.2, J1.2, J2.3, J2.4, Q2.3 (S), Q6.1 (E), R4.2, R7.2, R13.2, SW1.2, SW2.2, SW3.2, SW4.2, SW5.2, SW6.2

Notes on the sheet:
LITE control board - LEDs from a 4 x AA NiMH pack; keys straight to ESP32 GPIOs
The LEDs light only while ARM (GPIO2) powers them through Q5 AND the carrier on IR_DRV (GPIO17) switches Q2. LED head: 33 strings of 2 x SFH 4545 + 24R.
A. Battery, pack sense and LED power gate
Q5 (P-FET) connects the pack to the LEDs only while ARM is high. R14 holds it off; Q6 pulls its gate
down through R15 (Vgs = -0.91 x pack). C7 (gate-drain) is a soft start, C8 (gate-source) keeps Q5 off
when cells go in. R4 holds ARM low while the ESP32 boots. Pack sense: BATT / 2 (470k + 470k, 5 uA) on GPIO1.
B. LED switch (Q2) and LED head connector (J5)
J5 -> LED head J1 over the 10-way ribbon: odd pins VBAT (LED_PWR), even pins LED_RTN.
Q2 is logic-level (5.7 mOhm max at Vgs 2.5 V): GPIO17 drives it directly. R6 47R slows its edge so
the ribbon can't ring the LEDs into reverse bias (sim/). R7 holds Q2 off while the ESP32 boots.
C. J2 - Waveshare ESP32-S3-RLCD-4.2 2x8 header (16-way ribbon, pin n = pin n)
Used: 3/4 GND, 5 GPIO0 SELECT (also BOOT), 7 GPIO1 pack / 2, 9 GPIO2 ARM, 10 GPIO43 RIGHT (via R11), 11 GPIO3 DOWN,
12 GPIO44 LEFT, 13 GPIO17 IR_DRV, 15 GPIO18 UP (also KEY), 16 GPIO14 BACK (I2C SCL, 2.2k pull-up on the display board).
Not connected: 1 3V3, 2 VBUS, 6/8 USB D-/D+, 14 SDA. The display board and ESP32 run from their own 18650.
Mounting holes
D. Keys - each shorts its GPIO to GND; ESP32 internal pull-ups
R11: GPIO43 is UART TX during the boot ROM; 1k limits the current if RIGHT is held at power-up.

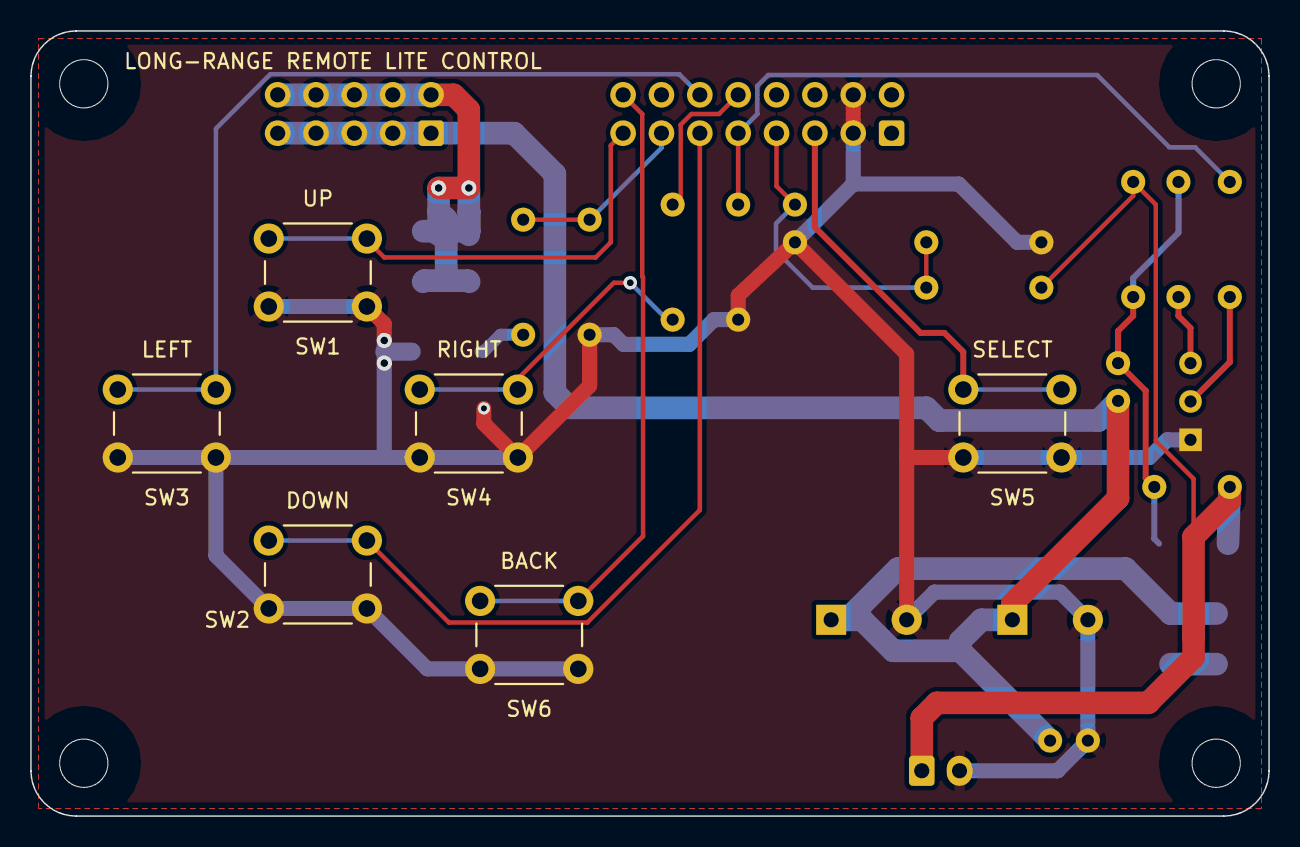
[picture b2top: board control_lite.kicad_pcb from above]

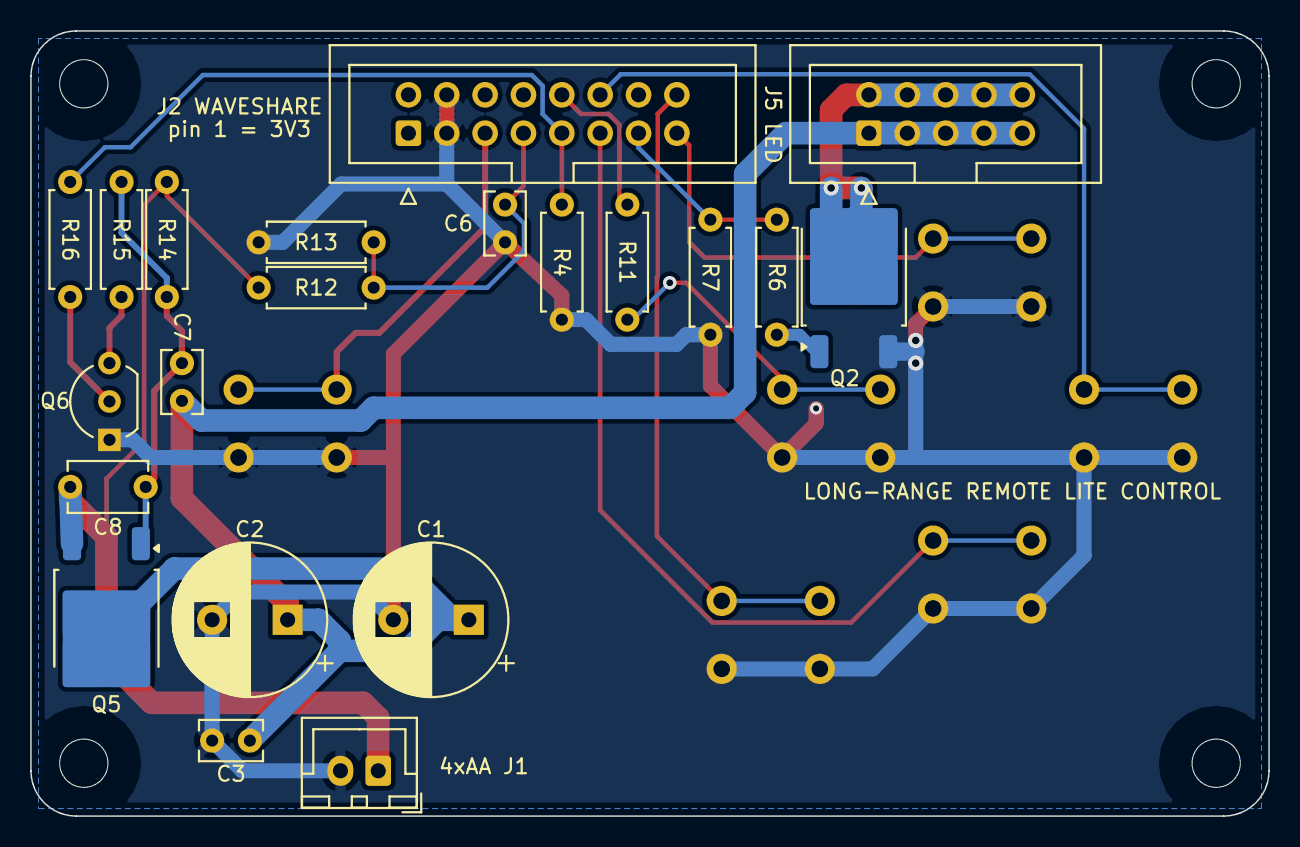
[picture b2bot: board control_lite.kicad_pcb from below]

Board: 2 copper layers, 82.0 x 52.0 mm, 31 parts (21 on the bottom side), 18 nets.
